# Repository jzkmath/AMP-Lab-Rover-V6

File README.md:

# AMP-Lab-Rover-V6
Low Cost Rover V6 Design Files.

This uses a Arduino Nano with Bluetooth Low Energy Module built-in to communicate with a smartphone through the Blynk App.

You will need to download the Blynk library to get the sketch to compile.

## Assembly Instructions

Video Tutorial: https://www.youtube.com/playlist?list=PL4FFrmT3l_b0y4ERLvnKdsL8f40yGXgXS

Written Manual: TBA

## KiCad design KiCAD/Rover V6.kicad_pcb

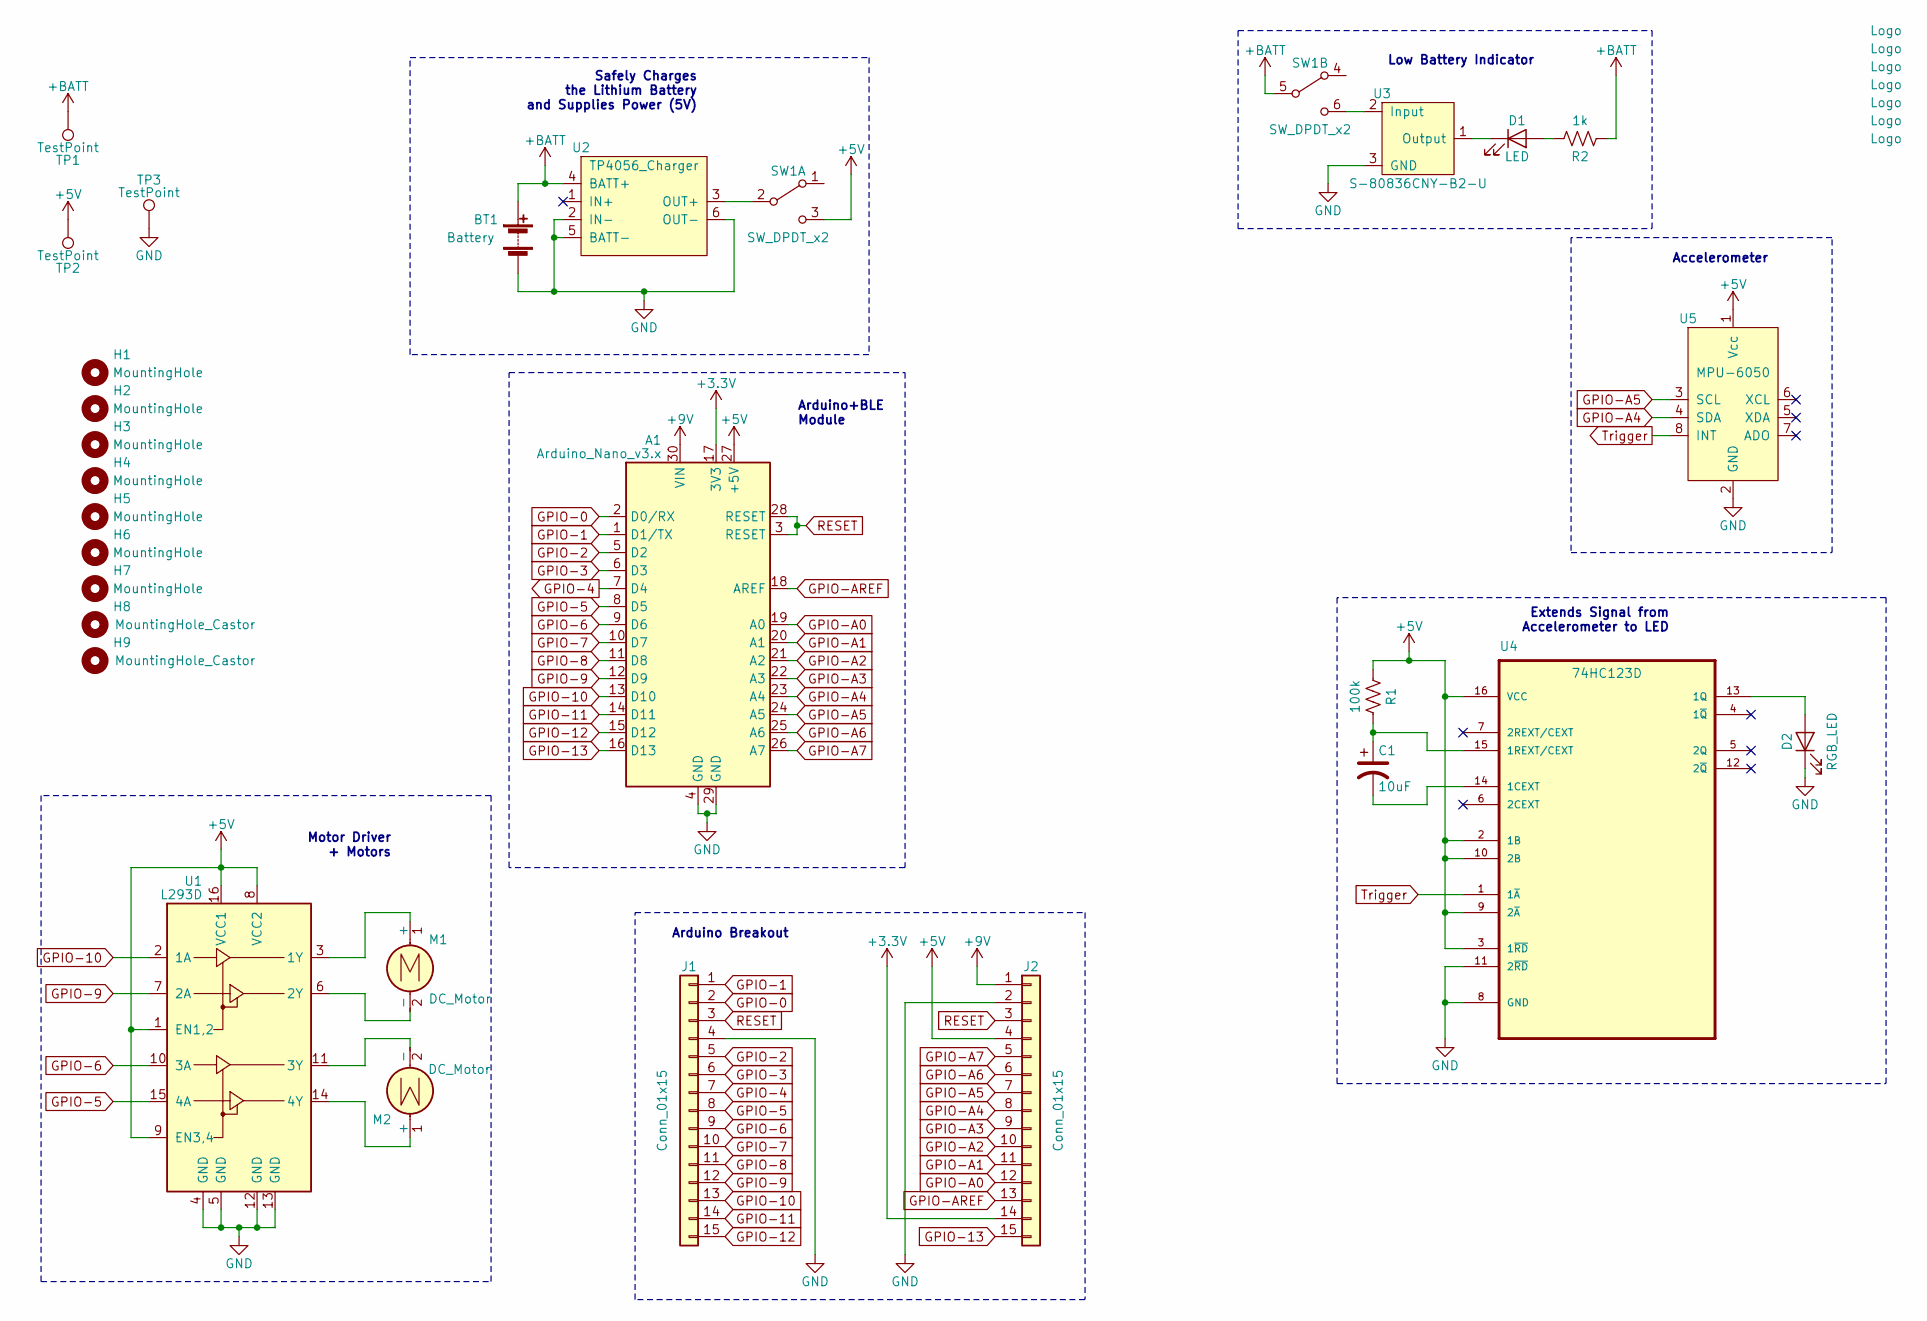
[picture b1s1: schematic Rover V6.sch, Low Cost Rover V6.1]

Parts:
A1: Arduino_Nano_v3.x; Arduino_Nano_Handsolder
BT1: Battery; 54x2; Digikey PN 36-54-ND
C1: 10uF; C_Disc_D4.3mm_W1.9mm_P5.00mm_Handsolder; Digikey PN 445-8396-ND
D1: LED; LED_D5.0mm_handsolder; Digikey PN C5SMF-RJF-CT0W0BB1-ND
D2: RGB_LED; LED_D5.0mm_handsolder
G1, G2: Logo; bolt
G3: Logo; bumper
G4, G5: Logo; flame
G6: Logo; flame_tiny
G7: Logo; LOGO2
H1, H2, H3, H4, H5, H6, H7: MountingHole; MountingHole_3.2mm_M3
H8: MountingHole_Castor; Ball_Caster
H9: MountingHole_Castor; Castor_Wheel
J1, J2: Conn_01x15; PinSocket_1x15_P2.54mm_Vertical_Handsolder
M1: DC_Motor; Motor
M2: DC_Motor; Motor_Mirror_true
R1: 100k; R_Combo; Digikey PN CF18JT100KCT-ND
R2: 1k; R_Combo; Digikey PN CF18JT1K00CT-ND
SW1: SW_DPDT_x2; Switch-EG2207; Digikey PN EG1940-ND
TP1, TP2, TP3: TestPoint; TestPoint_Pad_2.0x2.0mm
U1: L293D; DIP16_labeled; Digikey PN 497-2936-5-ND
U2: TP4056_Charger; TP4056_Module
U3: S-80836CNY-B2-U; TO-92_HandSolder; Digikey PN 1662-1815-ND
U4: 74HC123D; DIP16_labeled; Digikey PN TC74HC123APNEWF-ND
U5: MPU-6050; PinSocket_1x08_P2.54mm_Vertical_Zigzag

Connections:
+3V3: A1.17 (3V3), J2.14
+5V: A1.27 (+5V), J2.4, R1.1, SW1.3 (C), TP2.1, U1.1 (EN1,2), U1.8 (VCC2), U1.9 (EN3,4), U1.16 (VCC1), U4.2 (1B), U4.3 (1~RD), U4.9 (2~A), U4.10 (2B), U4.16 (VCC), U5.1 (Vcc)
+9V: A1.30 (VIN), J2.1
+BATT: BT1.1 (+), R2.1, SW1.5 (B), TP1.1, U2.4 (BATT+)
GND: A1.4 (GND), A1.29 (GND), BT1.2 (-), D2.1 (K), J1.4, J2.2, TP3.1, U1.4 (GND), U1.5 (GND), U1.12 (GND), U1.13 (GND), U2.2 (IN-), U2.5 (BATT-), U2.6 (OUT-), U3.3 (GND), U4.8 (GND), U4.11 (2~RD), U5.2 (GND)
GPIO-0: A1.2 (D0/RX), J1.2
GPIO-1: A1.1 (D1/TX), J1.1
GPIO-2: A1.5 (D2), J1.5
GPIO-3: A1.6 (D3), J1.6
GPIO-4: A1.7 (D4), J1.7
GPIO-5: A1.8 (D5), J1.8, U1.15 (4A)
GPIO-6: A1.9 (D6), J1.9, U1.10 (3A)
GPIO-7: A1.10 (D7), J1.10
GPIO-8: A1.11 (D8), J1.11
GPIO-9: A1.12 (D9), J1.12, U1.7 (2A)
GPIO-10: A1.13 (D10), J1.13, U1.2 (1A)
GPIO-11: A1.14 (D11), J1.14
GPIO-12: A1.15 (D12), J1.15
GPIO-13: A1.16 (D13), J2.15
GPIO-A0: A1.19 (A0), J2.12
GPIO-A1: A1.20 (A1), J2.11
GPIO-A2: A1.21 (A2), J2.10
GPIO-A3: A1.22 (A3), J2.9
GPIO-A4: A1.23 (A4), J2.8, U5.4 (SDA)
GPIO-A5: A1.24 (A5), J2.7, U5.3 (SCL)
GPIO-A6: A1.25 (A6), J2.6
GPIO-A7: A1.26 (A7), J2.5
GPIO-AREF: A1.18 (AREF), J2.13
unnamed: C1.1, R1.2, U4.15 (1REXT/CEXT)
unnamed: C1.2, U4.14 (1CEXT)
unnamed: D1.1 (K), U3.1 (Output)
unnamed: D1.2 (A), R2.2
unnamed: D2.2 (A), U4.13 (1Q)
unnamed: M1.1 (+), U1.3 (1Y)
unnamed: M1.2 (-), U1.6 (2Y)
unnamed: M2.1 (+), U1.14 (4Y)
unnamed: M2.2 (-), U1.11 (3Y)
unnamed: SW1.2 (B), U2.3 (OUT+)
unnamed: SW1.6 (C), U3.2 (Input)
RESET: A1.3 (RESET), A1.28 (RESET), J1.3, J2.3
Trigger: U4.1 (1~A), U5.8 (INT)

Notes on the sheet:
Low Battery Indicator
Accelerometer
Extends Signal from Accelerometer to LED
Motor Driver + Motors
Safely Charges the Lithium Battery and Supplies Power (5V)
Arduino+BLE Module
Arduino Breakout

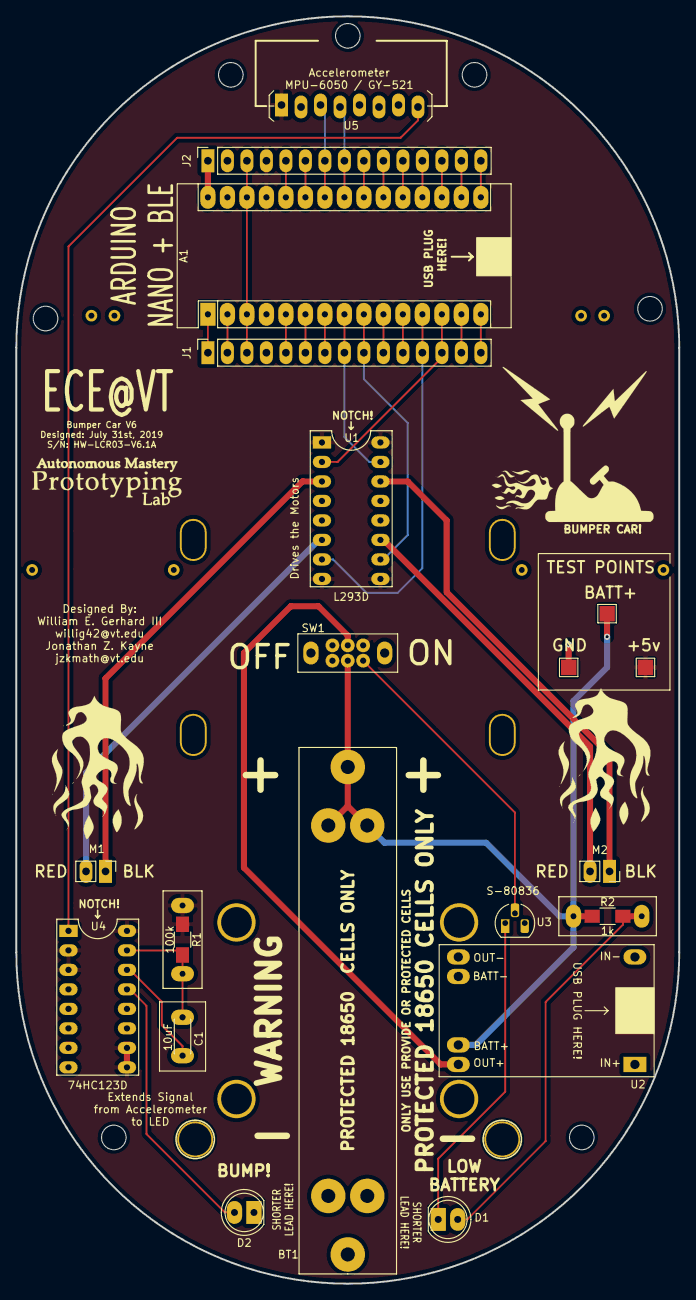
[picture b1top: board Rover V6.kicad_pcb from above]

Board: 2 copper layers, 86.4 x 165.1 mm, 36 parts (0 on the bottom side), 41 nets.

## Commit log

2019-07-31 Create jkjl
2019-07-31 Create jlkjl
2019-07-31 Create k;lk
2019-07-31 Adding KiCAD files
2019-07-31 Adding KiCAD files again
2019-08-09 Updated Arduino
2019-09-23 uploaded YouTube videos
